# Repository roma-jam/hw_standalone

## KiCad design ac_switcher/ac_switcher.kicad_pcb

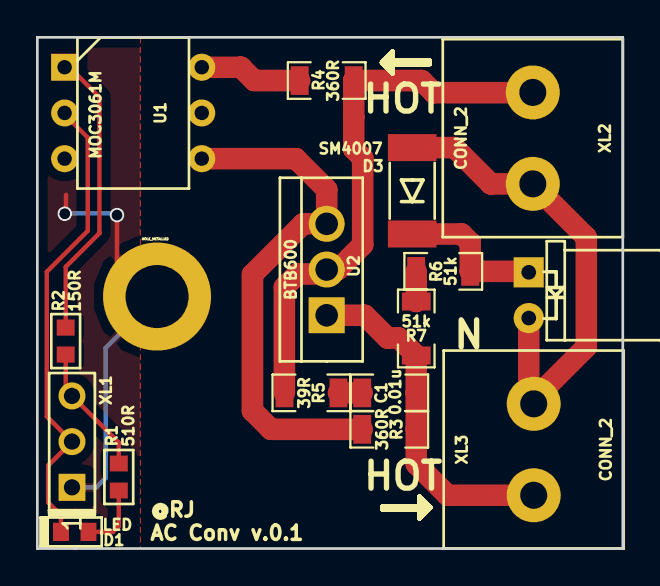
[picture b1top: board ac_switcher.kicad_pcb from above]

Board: 2 copper layers, 32.5 x 28.4 mm, 17 parts (0 on the bottom side), 13 nets.

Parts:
C1: 0.01u; CAP_1206
D1: LED; LED_0603
D2: LED; LED_Through-Hole-5mm-HOR
D3: SM4007; DIODE_MELF_DO213AB
HOLE1: HOLE_METALLED; Hole3_5_out6mm
R1: 510R; RES_0603
R2: 150R; RES_0603
R3, R4: 360R; RES_1206
R5: 39R; RES_1206
R6, R7: 51k; RES_1206
U1: MOC3061M; DIL6
U2: BTB600; TO220_VERTICAL
XL1: CONN_3; PLS-3
XL2, XL3: CONN_2; CONN_KF128D_2

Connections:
/AC1: R4.2, U1.6
/AC2: R3.1, U1.4, U2.3
/AC_FILT: C1.1, R5.2
/D1: D2.A, D3.C, R6.1
/D2: R6.2, R7.1
/HOT_IN: R4.1, R5.1, U2.2, XL2.1
/HOT_OUT: C1.2, R3.2, R7.2, U2.1, XL3.1
/NEUTRAL: D2.C, D3.A, XL2.2, XL3.2
GND: HOLE1.H, XL1.1
unnamed: D1.A, R1.2
unnamed: D1.C, U1.2, XL1.2
unnamed: R1.1, R2.2, XL1.3
unnamed: R2.1, U1.1

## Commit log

2019-05-31 + Add PCВ
2019-06-03 + Add ac switcher gerber files.
